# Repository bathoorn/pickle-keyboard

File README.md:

# pickle-keyboard
kicad pickle keyboard project

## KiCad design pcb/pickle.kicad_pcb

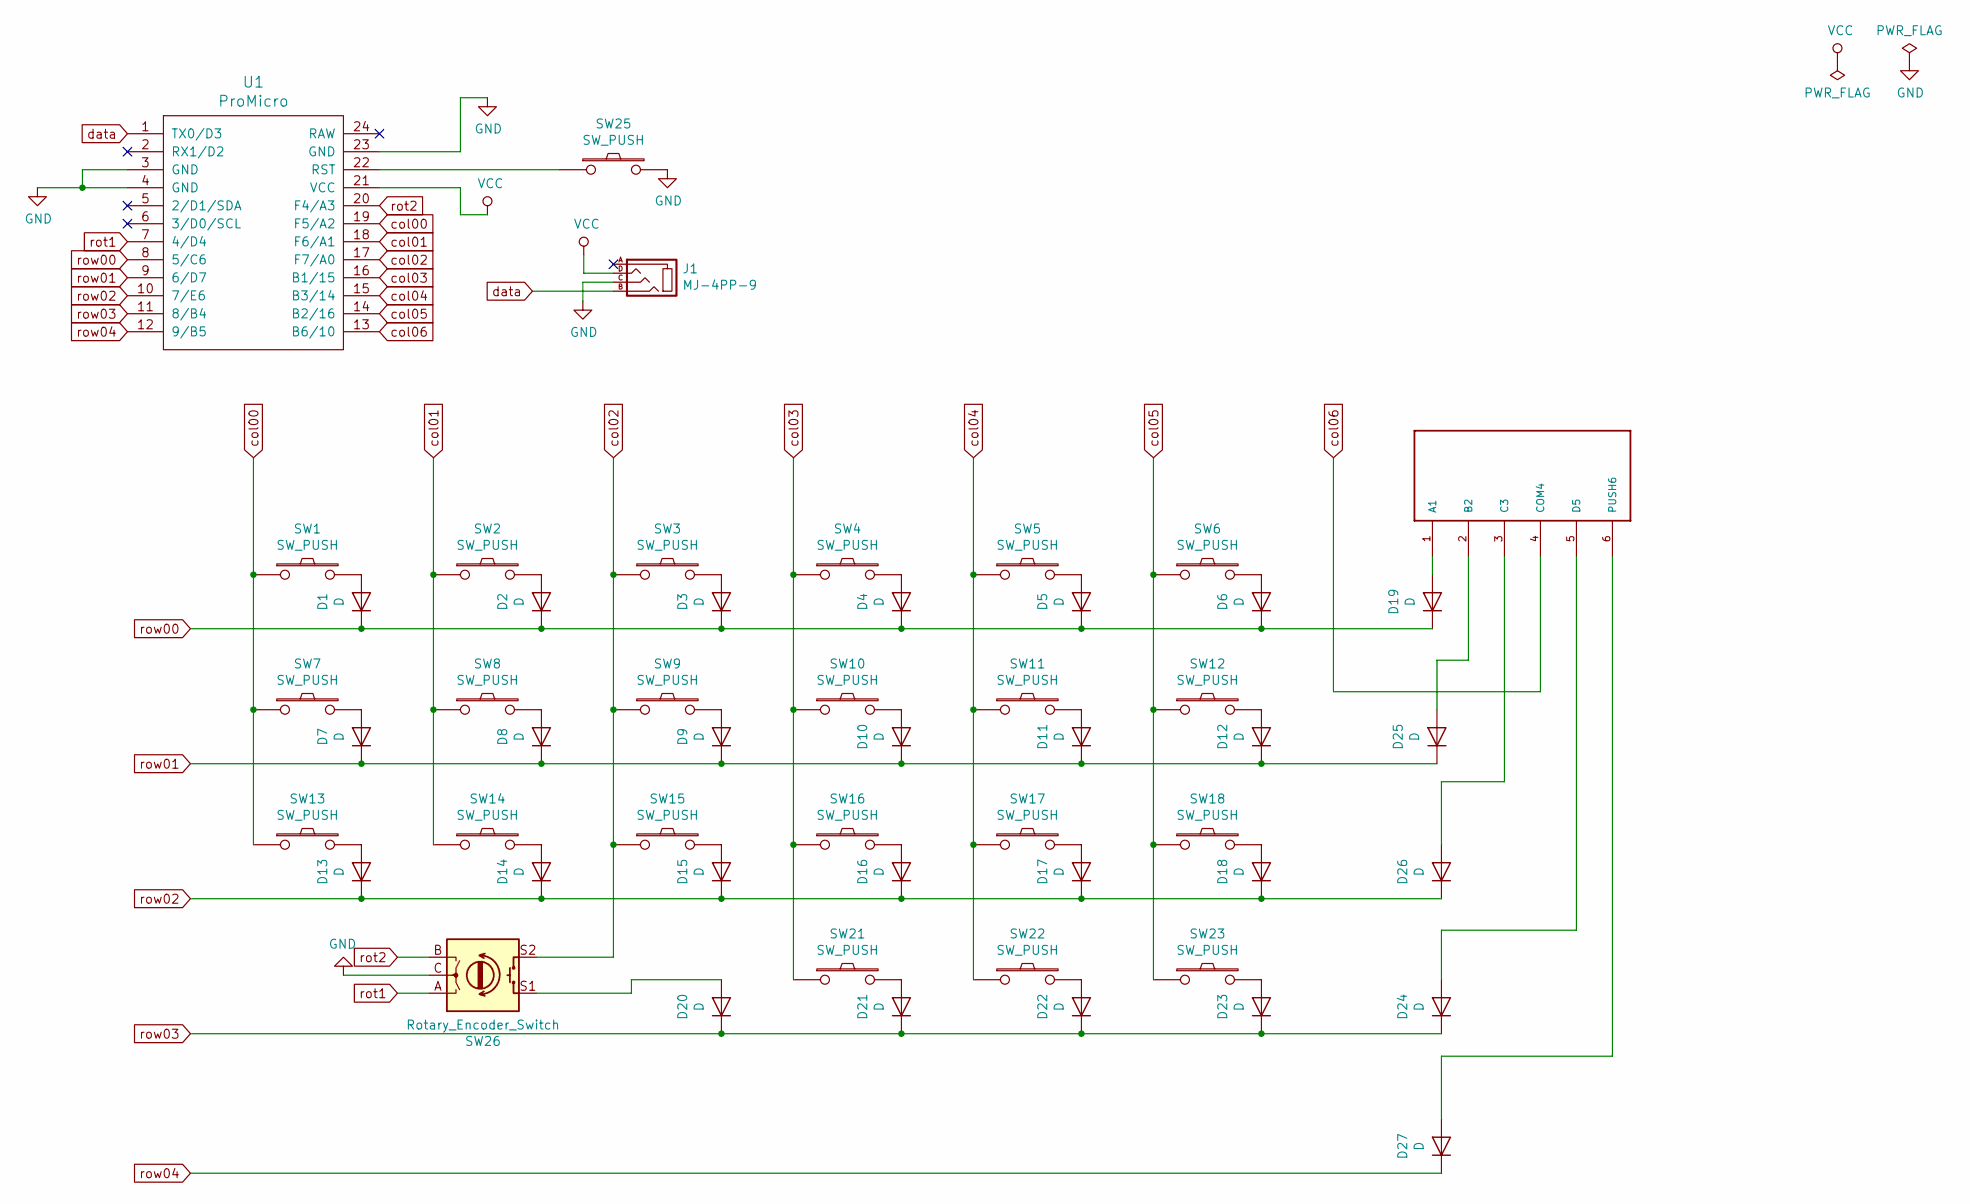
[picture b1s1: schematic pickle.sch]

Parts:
D1, D2, D3, D4, D5, D6, D7, D8, D9, D10, D11, D12, D13, D14, D15, D16, D17, D18, D19, D20, D21, D22, D23, D24, D25, D26, D27: D; D3_TH_SMD
J1: MJ-4PP-9
SW1, SW7, SW13: SW_PUSH; CherryMX_Hotswap_1.5u
SW2, SW3, SW4, SW5, SW6, SW8, SW9, SW10, SW11, SW12, SW14, SW15, SW16, SW17, SW18, SW21, SW22, SW23: SW_PUSH; CherryMX_Hotswap
SW25: SW_PUSH; ResetSW
SW26: Rotary_Encoder_Switch; RotaryEncoder_Alps_EC12E-Switch_Vertical_H20mm
U1: ProMicro; ProMicro_v2
U2: SKQUAAA010

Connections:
GND: J1.C, SW25.2, SW26.C, U1.3 (GND), U1.4 (GND), U1.23 (GND)
unnamed: D1.2 (A), SW1.2
unnamed: D2.2 (A), SW2.2
unnamed: D3.2 (A), SW3.2
unnamed: D4.2 (A), SW4.2
unnamed: D5.2 (A), SW5.2
unnamed: D6.2 (A), SW6.2
unnamed: D7.2 (A), SW7.2
unnamed: D8.2 (A), SW8.2
unnamed: D9.2 (A), SW9.2
unnamed: D10.2 (A), SW10.2
unnamed: D11.2 (A), SW11.2
unnamed: D12.2 (A), SW12.2
unnamed: D13.2 (A), SW13.2
unnamed: D14.2 (A), SW14.2
unnamed: D15.2 (A), SW15.2
unnamed: D16.2 (A), SW16.2
unnamed: D17.2 (A), SW17.2
unnamed: D18.2 (A), SW18.2
unnamed: D19.2 (A), U2.1 (A1)
unnamed: D20.2 (A), SW26.S1
unnamed: D21.2 (A), SW21.2
unnamed: D22.2 (A), SW22.2
unnamed: D23.2 (A), SW23.2
unnamed: D24.2 (A), U2.5 (D5)
unnamed: D25.2 (A), U2.2 (B2)
unnamed: D26.2 (A), U2.3 (C3)
unnamed: D27.2 (A), U2.6 (PUSH6)
unnamed: SW25.1, U1.22 (RST)
VCC: J1.D, U1.21 (VCC)
col00: SW1.1, SW7.1, SW13.1, U1.19 (F5/A2)
col01: SW2.1, SW8.1, SW14.1, U1.18 (F6/A1)
col02: SW3.1, SW9.1, SW15.1, SW26.S2, U1.17 (F7/A0)
col03: SW4.1, SW10.1, SW16.1, SW21.1, U1.16 (B1/15)
col04: SW5.1, SW11.1, SW17.1, SW22.1, U1.15 (B3/14)
col05: SW6.1, SW12.1, SW18.1, SW23.1, U1.14 (B2/16)
col06: U1.13 (B6/10), U2.4 (COM4)
data: J1.B, U1.1 (TX0/D3)
rot1: SW26.A, U1.7 (4/D4)
rot2: SW26.B, U1.20 (F4/A3)
row00: D1.1 (K), D2.1 (K), D3.1 (K), D4.1 (K), D5.1 (K), D6.1 (K), D19.1 (K), U1.8 (5/C6)
row01: D7.1 (K), D8.1 (K), D9.1 (K), D10.1 (K), D11.1 (K), D12.1 (K), D25.1 (K), U1.9 (6/D7)
row02: D13.1 (K), D14.1 (K), D15.1 (K), D16.1 (K), D17.1 (K), D18.1 (K), D26.1 (K), U1.10 (7/E6)
row03: D20.1 (K), D21.1 (K), D22.1 (K), D23.1 (K), D24.1 (K), U1.11 (8/B4)
row04: D27.1 (K), U1.12 (9/B5)

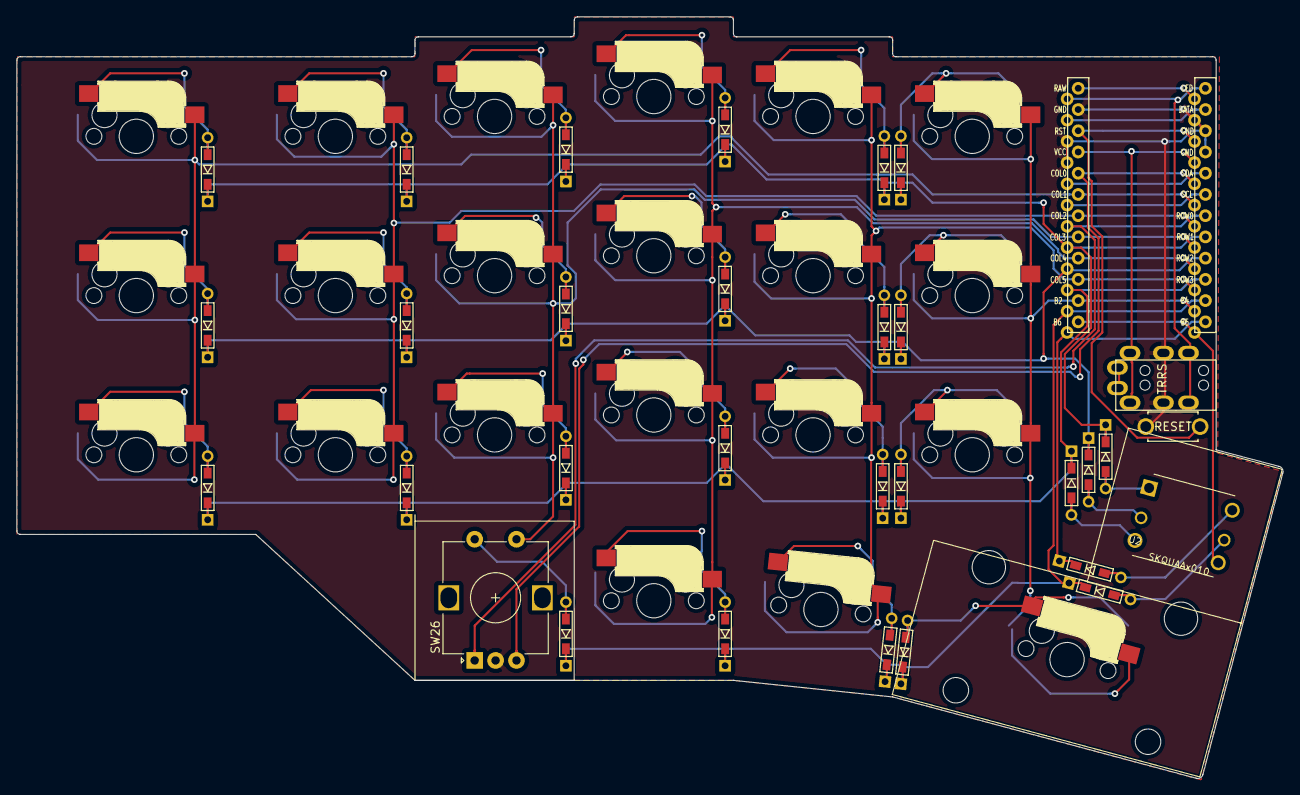
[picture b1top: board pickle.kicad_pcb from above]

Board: 2 copper layers, 151.5 x 91.1 mm, 53 parts (0 on the bottom side), 45 nets.

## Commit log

2020-04-01 add kicad files
